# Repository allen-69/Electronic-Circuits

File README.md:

PCB Designing Course Internship June 2026 by Allen Joshua S

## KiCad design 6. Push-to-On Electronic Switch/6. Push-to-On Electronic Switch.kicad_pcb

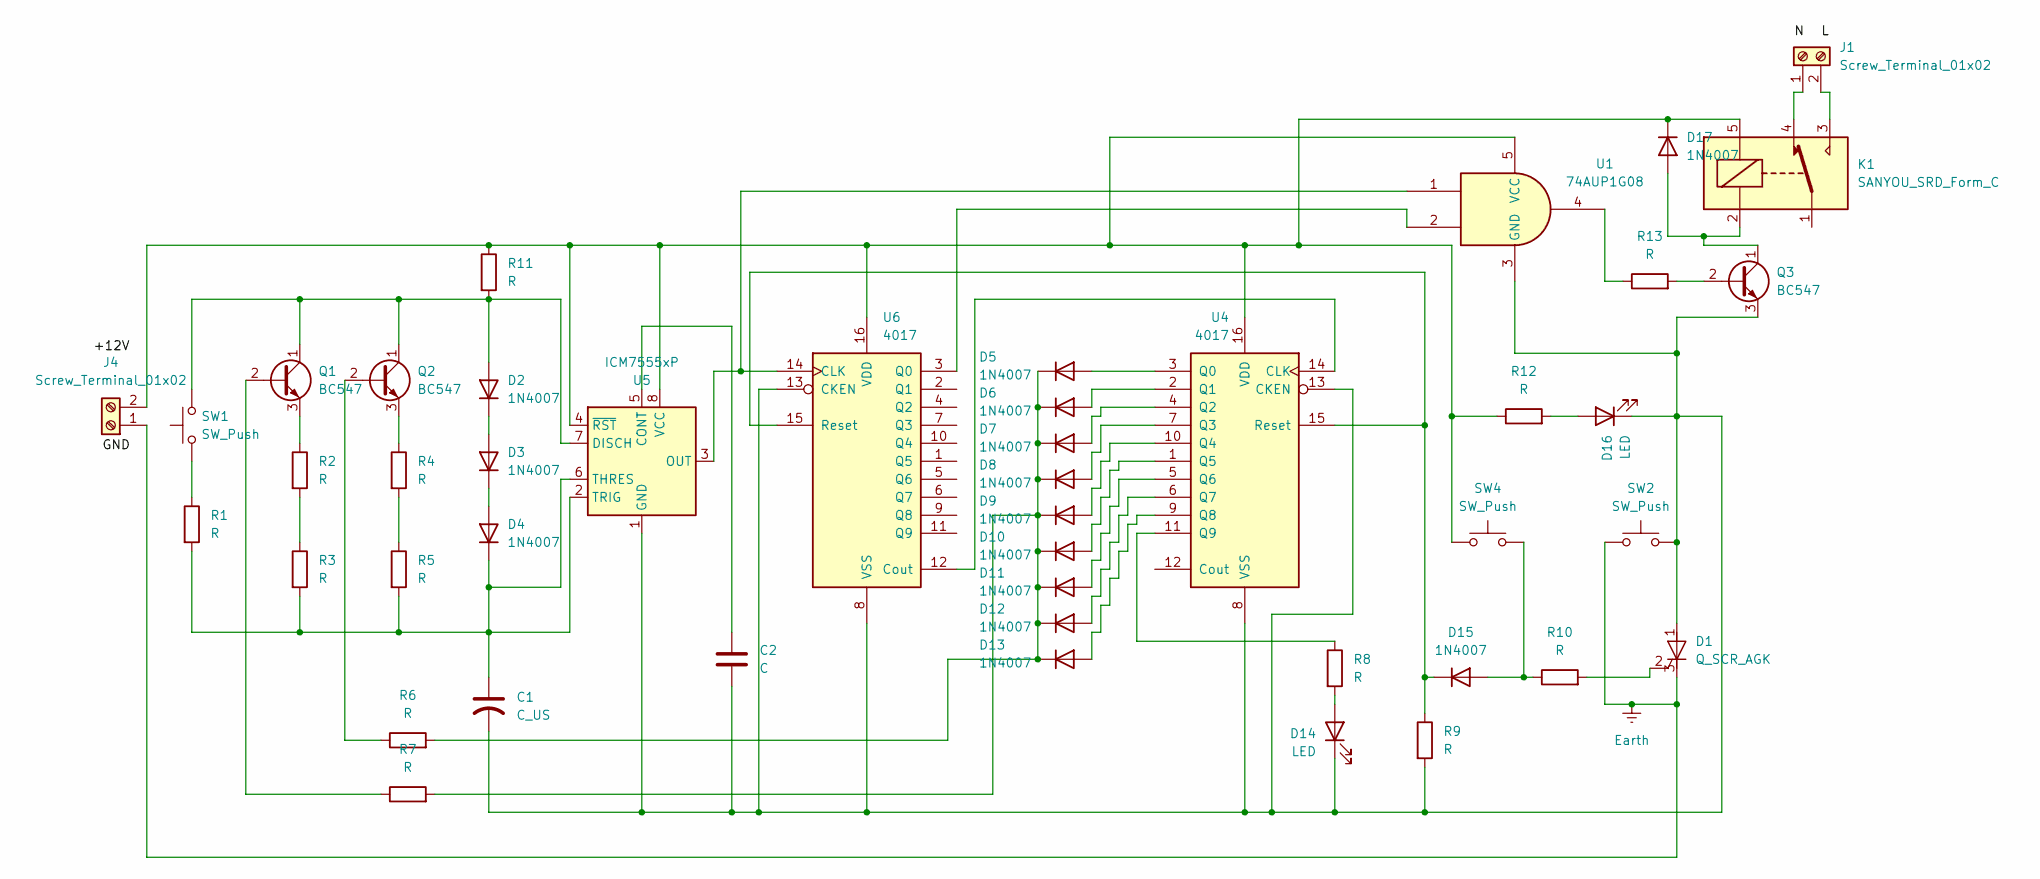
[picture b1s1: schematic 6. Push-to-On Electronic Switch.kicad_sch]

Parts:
C1: C_US; C_Radial_D4.0mm_H5.0mm_P1.50mm
C2: C; C_Radial_D5.0mm_H5.0mm_P2.00mm
D1: Q_SCR_AGK; TO-220-3_Vertical
D2, D3, D4, D5, D6, D7, D8, D9, D10, D11, D12, D13, D15, D17: 1N4007; D_DO-41_SOD81_P10.16mm_Horizontal
D14, D16: LED; LED_D3.0mm
J1, J4: Screw_Terminal_01x02; TerminalBlock_RND_205-00067_1x02_P7.50mm_Horizontal
K1: SANYOU_SRD_Form_C; Relay_SPDT_SANYOU_SRD_Series_Form_C
Q1, Q2, Q3: BC547; TO-92_Inline
R1, R2, R3, R4, R5, R6, R7, R8, R9, R10, R11, R12, R13: R; R_Axial_DIN0207_L6.3mm_D2.5mm_P15.24mm_Horizontal
SW1, SW2, SW4: SW_Push; SW_Tactile_Straight_KSA0Axx1LFTR
U1: 74AUP1G08; Texas_R-PDSO-G5_DCK-5
U4, U6: 4017; CERDIP-16_W7.62mm_SideBrazed_LongPads
U5: ICM7555xP; DIP-8_W7.62mm

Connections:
Earth: D1.3 (K), J4.1, SW2.1
unnamed: C1.2, C2.2, D1.1 (A), D14.1 (K), D16.1 (K), Q3.3 (E), R9.2, SW2.2, U1.3 (GND), U4.8 (VSS), U4.13 (CKEN), U5.1 (GND), U6.8 (VSS), U6.13 (CKEN)
unnamed: D1.2 (G), R10.2
unnamed: D2.2 (A), Q1.1 (C), Q2.1 (C), R11.2, SW1.2, U5.7 (DISCH)
unnamed: D2.1 (K), D3.2 (A)
unnamed: D3.1 (K), D4.2 (A)
unnamed: C1.1, D4.1 (K), R1.2, R3.2, R5.2, U5.2 (TRIG), U5.6 (THRES)
unnamed: D5.2 (A), U4.3 (Q0)
unnamed: D6.2 (A), U4.2 (Q1)
unnamed: D7.2 (A), U4.4 (Q2)
unnamed: D8.2 (A), U4.7 (Q3)
unnamed: D9.2 (A), U4.10 (Q4)
unnamed: D10.2 (A), U4.1 (Q5)
unnamed: D5.1 (K), D6.1 (K), D7.1 (K), D8.1 (K), D9.1 (K), D10.1 (K), D11.1 (K), D12.1 (K), D13.1 (K), R6.2, R7.2
unnamed: D11.2 (A), U4.5 (Q6)
unnamed: D12.2 (A), U4.6 (Q7)
unnamed: D13.2 (A), U4.9 (Q8)
unnamed: D14.2 (A), R8.2
unnamed: D15.2 (A), R10.1, SW4.2
unnamed: D15.1 (K), R9.1, U4.15 (Reset), U6.15 (Reset)
unnamed: D16.2 (A), R12.2
unnamed: D17.2 (A), K1.2, Q3.1 (C)
unnamed: D17.1 (K), J4.2, K1.5, R11.1, R12.1, SW4.1, U1.5 (VCC), U4.16 (VDD), U5.4 (~RST), U5.8 (VCC), U6.16 (VDD)
unnamed: J1.1, K1.4
unnamed: J1.2, K1.3
unnamed: Q1.2 (B), R7.1
unnamed: Q1.3 (E), R2.1
unnamed: Q2.2 (B), R6.1
unnamed: Q2.3 (E), R4.1
unnamed: Q3.2 (B), R13.2
unnamed: R1.1, SW1.1
unnamed: R2.2, R3.1
unnamed: R4.2, R5.1
unnamed: R13.1, U1.4
unnamed: U4.14 (CLK), U6.12 (Cout)
unnamed: R8.1, U4.11 (Q9)
unnamed: C2.1, U5.5 (CONT)
unnamed: U1.1, U5.3 (OUT), U6.14 (CLK)
unnamed: U1.2, U6.3 (Q0)

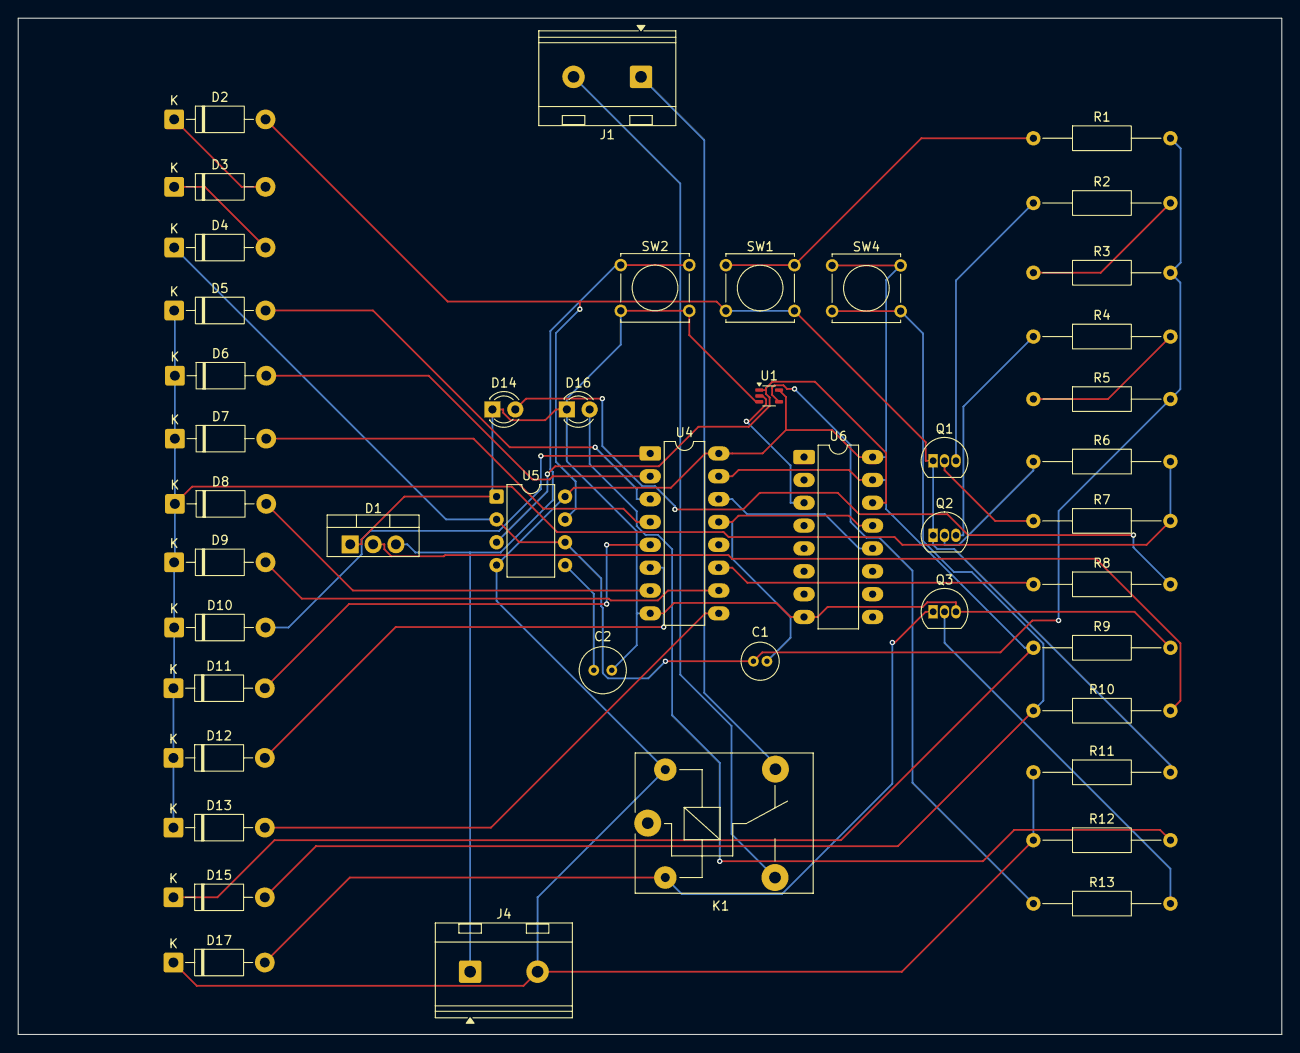
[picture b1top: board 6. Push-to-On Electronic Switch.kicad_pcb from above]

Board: 2 copper layers, 140.5 x 113.0 mm, 45 parts (0 on the bottom side), 39 nets.

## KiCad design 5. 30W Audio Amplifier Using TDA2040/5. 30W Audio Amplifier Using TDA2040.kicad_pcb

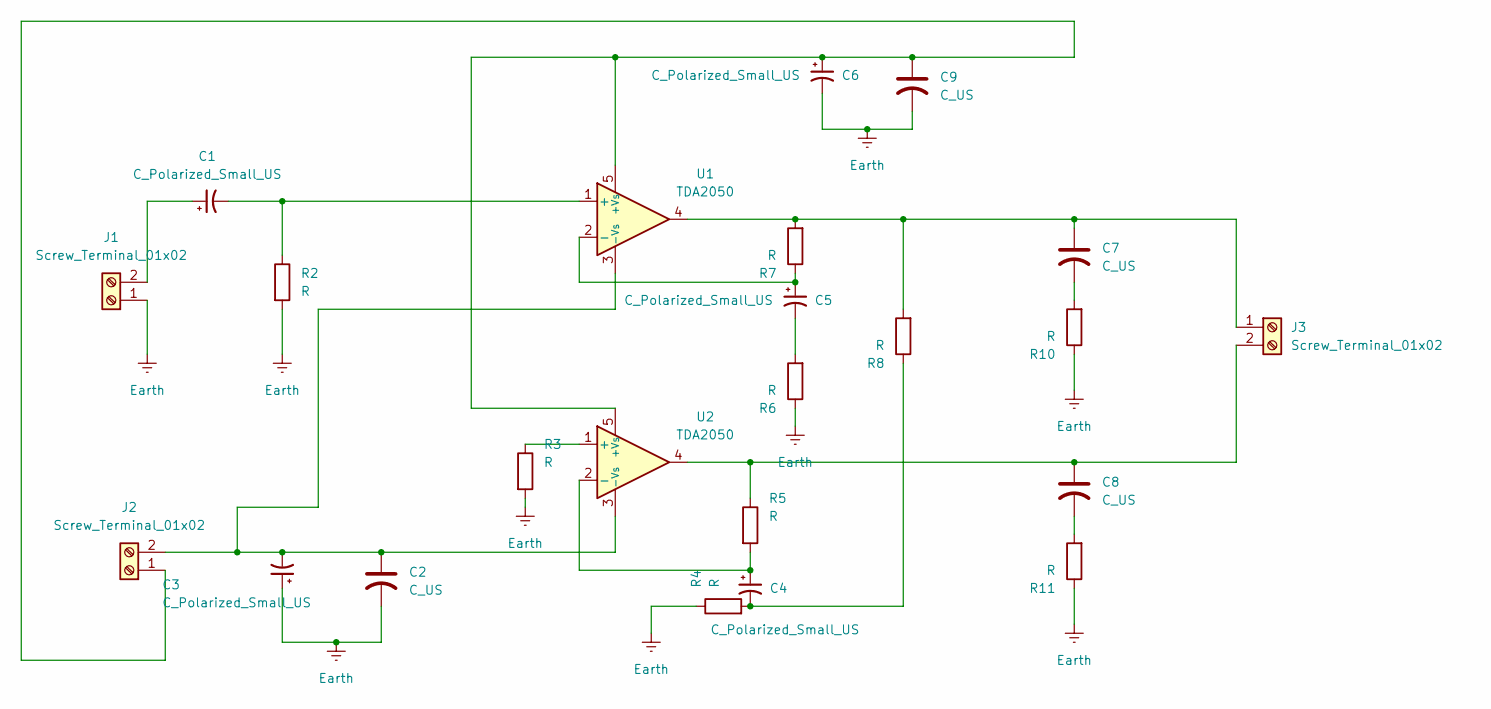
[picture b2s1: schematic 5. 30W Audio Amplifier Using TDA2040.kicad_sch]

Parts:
C1, C3, C4, C5, C6: C_Polarized_Small_US; CP_Radial_Tantal_D8.0mm_P5.00mm
C2, C7, C8, C9: C_US; C_Radial_D6.3mm_H5.0mm_P2.50mm
J1, J2, J3: Screw_Terminal_01x02; TerminalBlock_RND_205-00001_1x02_P5.00mm_Horizontal
R2, R3, R4, R5, R6, R7, R8, R10, R11: R; R_Axial_DIN0309_L9.0mm_D3.2mm_P12.70mm_Horizontal
U1, U2: TDA2050; TO-220-5_P3.4x3.7mm_StaggerOdd_Lead3.8mm_Vertical

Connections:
Earth: C2.2, C3.1, C6.2, C9.2, J1.1, R2.2, R3.2, R4.1, R6.1, R10.1, R11.1
unnamed: C4.2, R4.2, R8.1
unnamed: C5.2, R6.2
unnamed: C7.2, R10.2
unnamed: C8.2, R11.2
unnamed: C1.1, J1.2
unnamed: C6.1, C9.1, J2.1, U1.5 (+Vs), U2.5 (+Vs)
unnamed: C2.1, C3.2, J2.2, U1.3 (-Vs), U2.3 (-Vs)
unnamed: C7.1, J3.1, R7.2, R8.2, U1.4
unnamed: C8.1, J3.2, R5.1, U2.4
unnamed: C1.2, R2.1, U1.1 (+)
unnamed: C5.1, R7.1, U1.2 (-)
unnamed: R3.1, U2.1 (+)
unnamed: C4.1, R5.2, U2.2 (-)

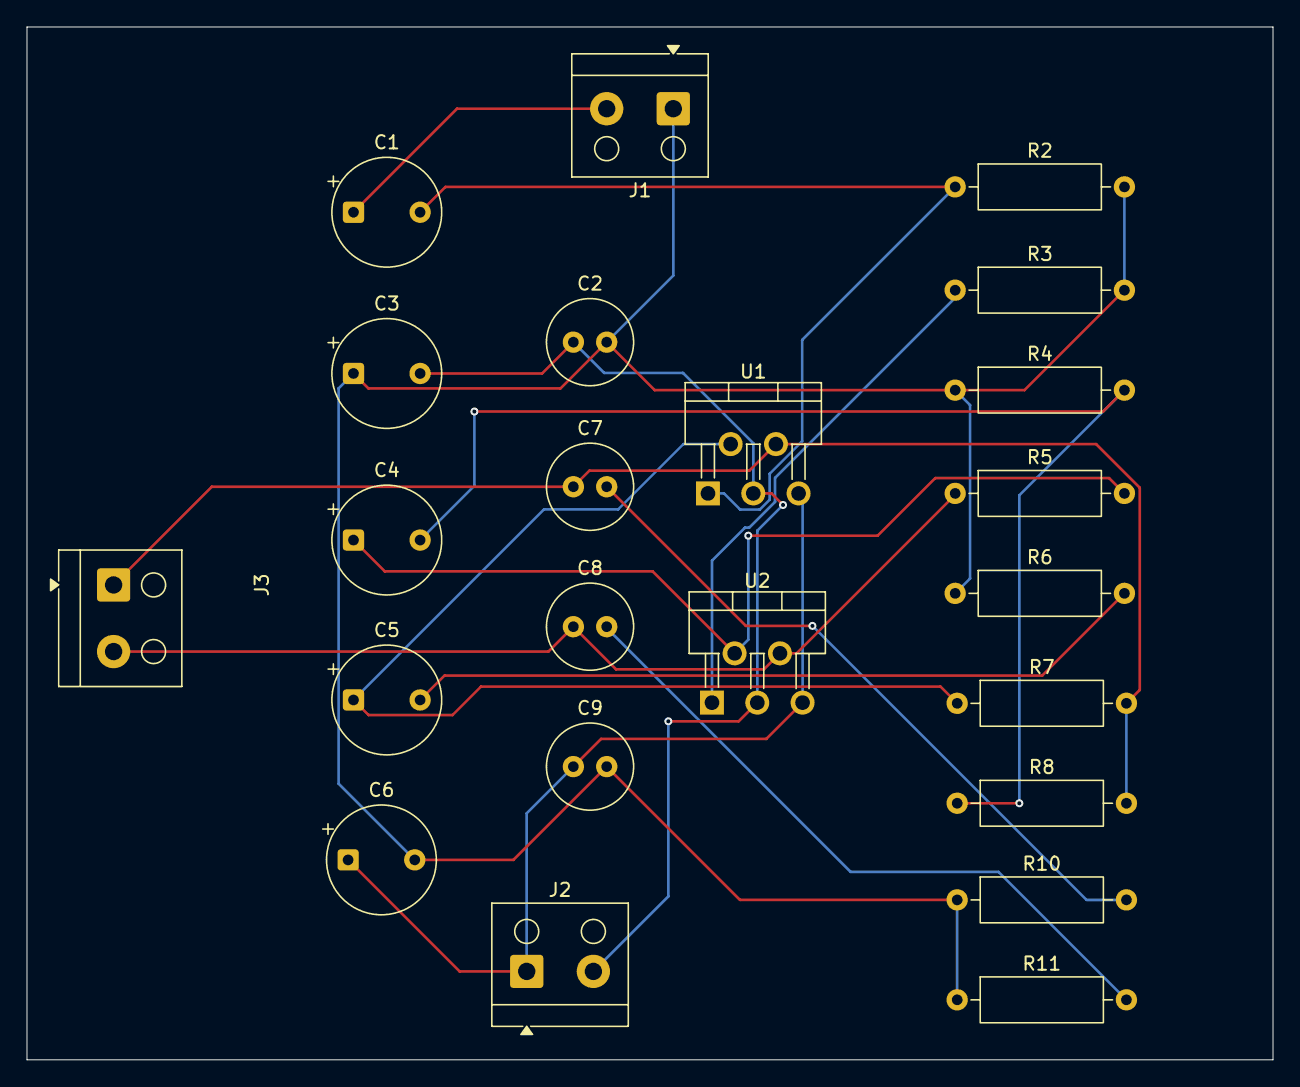
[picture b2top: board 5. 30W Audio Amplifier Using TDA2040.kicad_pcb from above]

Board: 2 copper layers, 93.5 x 77.5 mm, 23 parts (0 on the bottom side), 14 nets.

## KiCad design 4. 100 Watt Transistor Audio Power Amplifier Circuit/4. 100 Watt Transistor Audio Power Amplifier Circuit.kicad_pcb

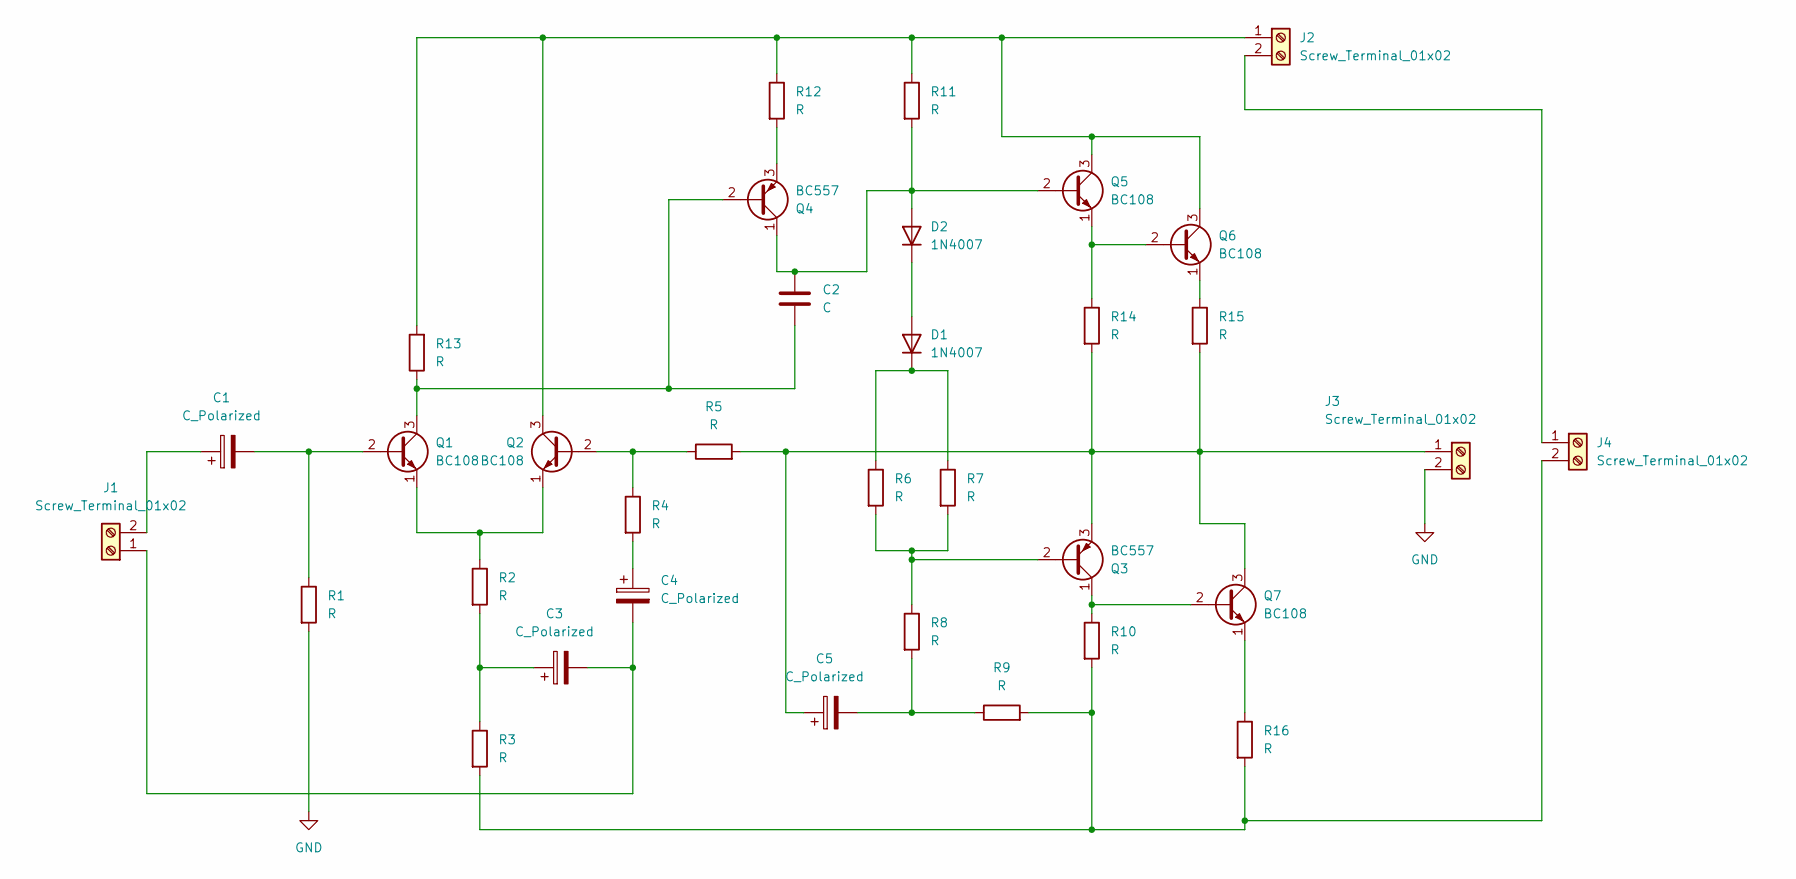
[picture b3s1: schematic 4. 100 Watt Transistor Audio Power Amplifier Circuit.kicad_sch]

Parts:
C1, C3, C4, C5: C_Polarized; CP_Radial_D13.0mm_P5.00mm
C2: C; C_Radial_D5.0mm_H11.0mm_P2.00mm
D1, D2: 1N4007; D_DO-41_SOD81_P10.16mm_Horizontal
J1, J2, J3, J4: Screw_Terminal_01x02; TerminalBlock_RND_205-00012_1x02_P5.00mm_Horizontal
Q1, Q2, Q5, Q6, Q7: BC108; TO-18-3
Q3, Q4: BC557; TO-92_Inline
R1, R2, R3, R4, R5, R6, R7, R8, R9, R10, R11, R12, R13, R14, R15, R16: R; R_Axial_DIN0207_L6.3mm_D2.5mm_P7.62mm_Horizontal

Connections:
GND: J3.2, R1.2
unnamed: C3.1, R2.2, R3.1
unnamed: C4.1, R4.2
unnamed: C5.2, R8.2, R9.1
unnamed: D1.2 (A), D2.1 (K)
unnamed: D1.1 (K), R6.1, R7.1
unnamed: C2.1, D2.2 (A), Q4.1 (C), Q5.2 (B), R11.2
unnamed: C3.2, C4.2, J1.1
unnamed: C1.1, J1.2
unnamed: J2.1, Q2.3 (C), Q5.3 (C), Q6.3 (C), R11.1, R12.1, R13.2
unnamed: J2.2, J4.1
unnamed: C5.1, J3.1, Q3.3 (E), Q7.3 (C), R5.2, R14.2, R15.2
unnamed: J4.2, R3.2, R9.2, R10.2, R16.2
unnamed: C1.2, Q1.2 (B), R1.1
unnamed: C2.2, Q1.3 (C), Q4.2 (B), R13.1
unnamed: Q1.1 (E), Q2.1 (E), R2.1
unnamed: Q2.2 (B), R4.1, R5.1
unnamed: Q3.2 (B), R6.2, R7.2, R8.1
unnamed: Q3.1 (C), Q7.2 (B), R10.1
unnamed: Q4.3 (E), R12.2
unnamed: Q5.1 (E), Q6.2 (B), R14.1
unnamed: Q6.1 (E), R15.1
unnamed: Q7.1 (E), R16.1

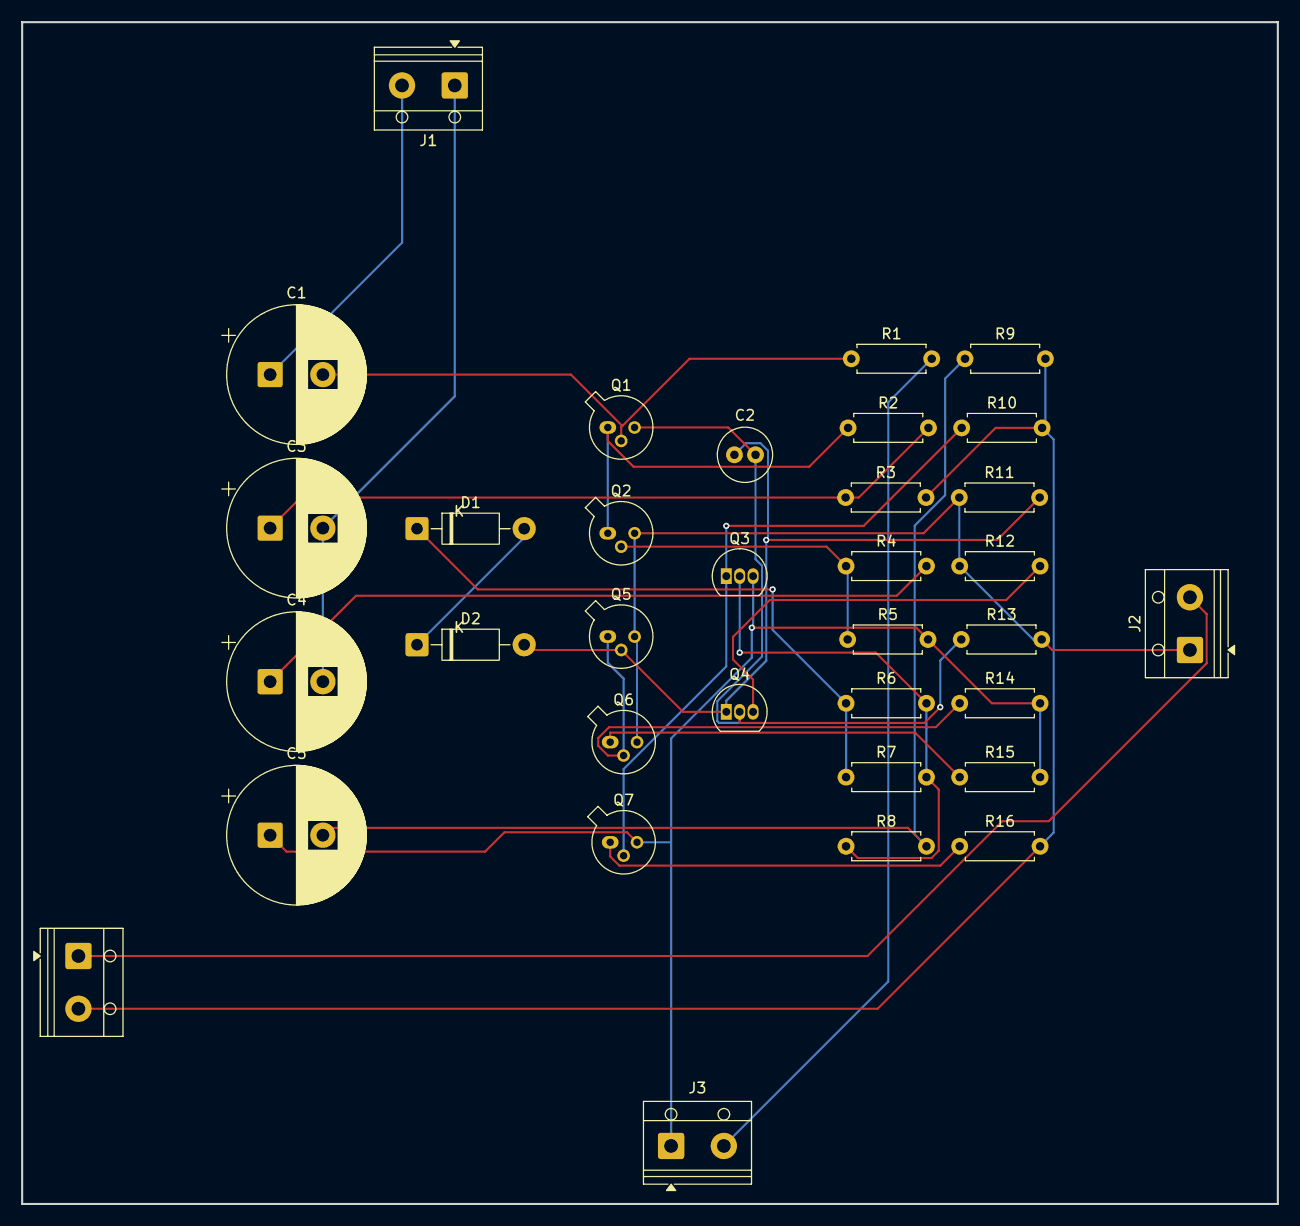
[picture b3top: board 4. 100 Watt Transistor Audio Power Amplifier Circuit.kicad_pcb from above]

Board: 2 copper layers, 119.0 x 112.0 mm, 34 parts (0 on the bottom side), 23 nets.

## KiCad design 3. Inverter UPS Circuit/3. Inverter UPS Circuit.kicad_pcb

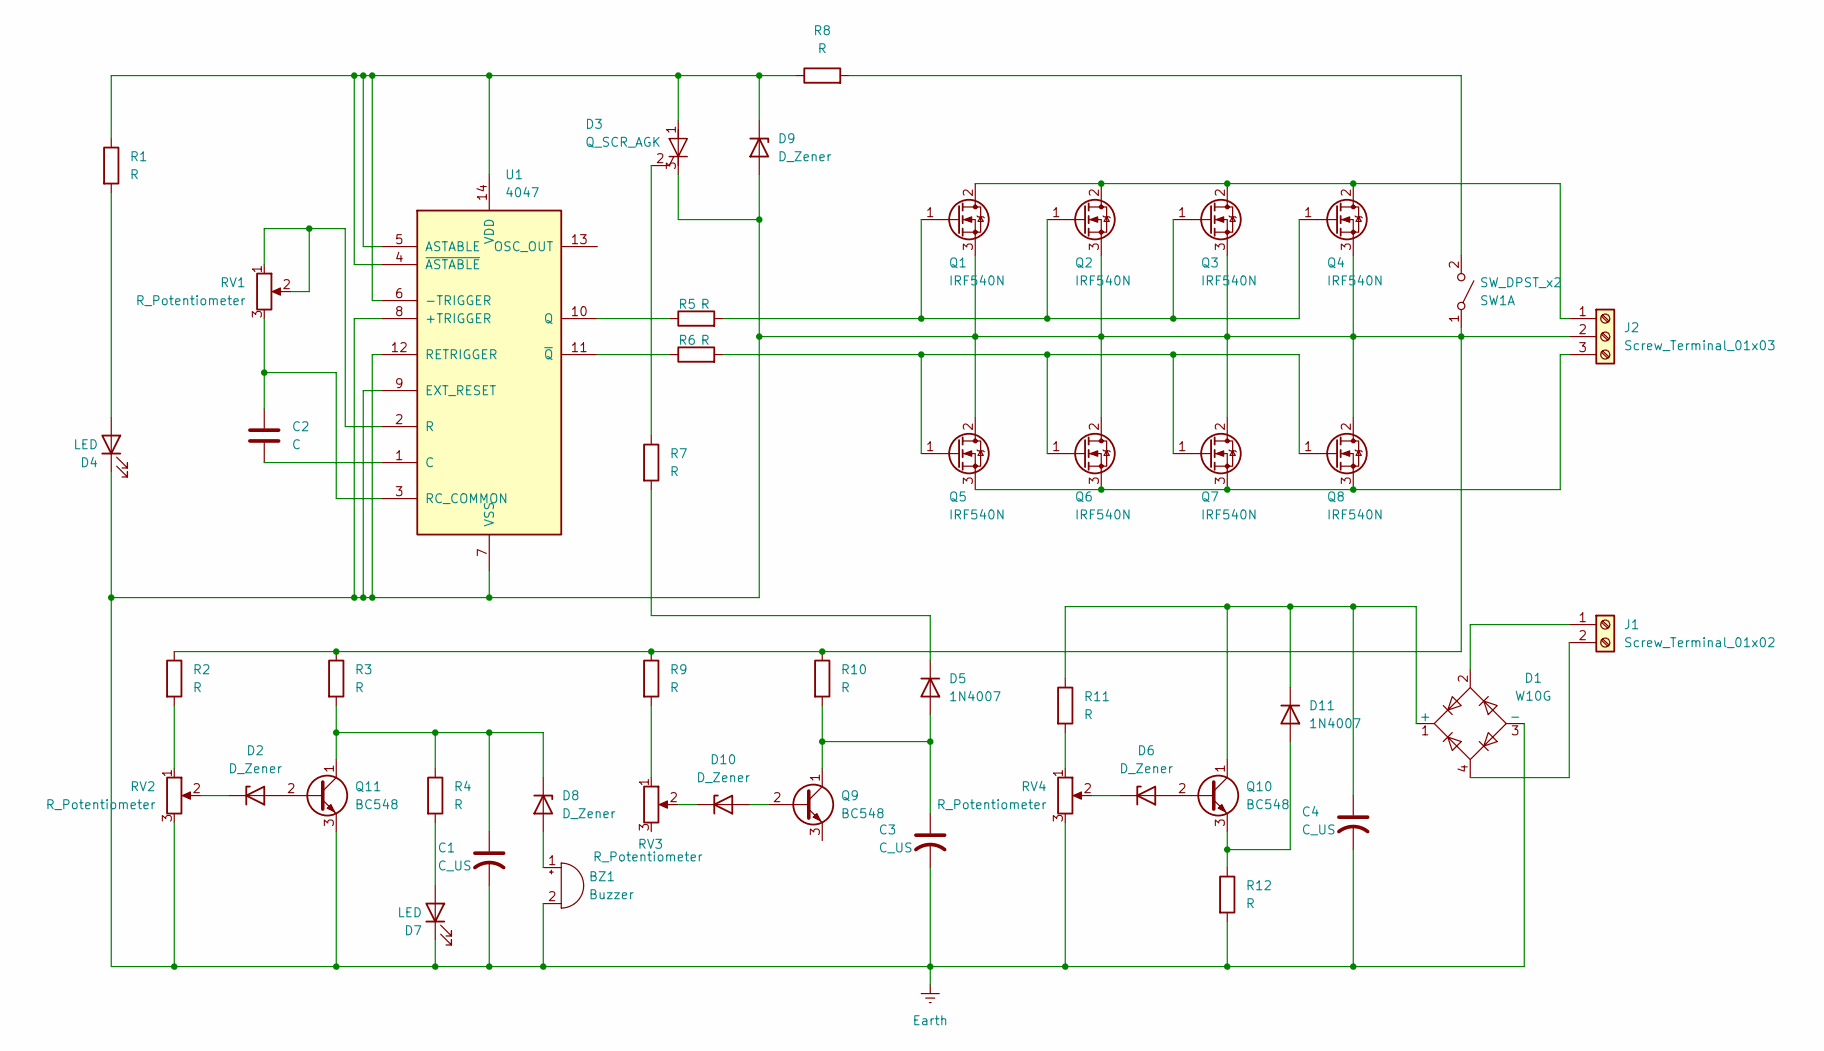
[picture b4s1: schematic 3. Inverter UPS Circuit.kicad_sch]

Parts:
BZ1: Buzzer; Buzzer_12x9.5RM7.6
C1, C3, C4: C_US; C_Radial_D4.0mm_H5.0mm_P1.50mm
C2: C; C_Radial_D6.3mm_H5.0mm_P2.50mm
D1: W10G; Diode_Bridge_Round_D9.8mm
D2, D6, D8, D9, D10: D_Zener; D_5W_P12.70mm_Horizontal
D3: Q_SCR_AGK; SW_Slide-03_Wuerth-WS-SLTV_10x2.5x6.4_P2.54mm
D4, D7: LED; LED_D3.0mm
D5, D11: 1N4007; D_DO-41_SOD81_P10.16mm_Horizontal
J1: Screw_Terminal_01x02; TerminalBlock_RND_205-00001_1x02_P5.00mm_Horizontal
J2: Screw_Terminal_01x03; TerminalBlock_RND_205-00002_1x03_P5.00mm_Horizontal
Q1, Q2, Q3, Q4, Q5, Q6, Q7, Q8: IRF540N; TO-220-3_Vertical
Q9, Q10, Q11: BC548; TO-92_Inline
R1, R2, R3, R4, R5, R6, R7, R8, R9, R10, R11, R12: R; R_Axial_DIN0204_L3.6mm_D1.6mm_P7.62mm_Horizontal
RV1, RV2, RV3, RV4: R_Potentiometer; Potentiometer_ACP_CA14V-15_Vertical
SW1: SW_DPST_x2; SW_DIP_SPSTx02_Piano_10.8x6.64mm_W7.62mm_P2.54mm
U1: 4047; DIP-14_W7.62mm_Socket

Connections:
Earth: BZ1.2 (-), C1.2, C3.2, C4.2, D1.3 (-), D3.3 (K), D4.1 (K), D7.1 (K), D9.2 (A), J2.2, Q1.3 (S), Q2.3 (S), Q3.3 (S), Q4.3 (S), Q5.2 (D), Q6.2 (D), Q7.2 (D), Q8.2 (D), Q11.3 (E), R2.1, R3.1, R9.1, R10.1, R12.2, RV2.3, RV4.3, SW1.1 (A), U1.7 (VSS), U1.8 (+TRIGGER), U1.9 (EXT_RESET), U1.12 (RETRIGGER)
unnamed: BZ1.1 (+), D8.2 (A)
unnamed: C4.1, D1.1 (+), D11.1 (K), Q10.1 (C), R11.1
unnamed: D2.2 (A), Q11.2 (B)
unnamed: D2.1 (K), RV2.2
unnamed: D3.1 (A), D9.1 (K), R1.1, R8.1, U1.4 (~ASTABLE), U1.5 (ASTABLE), U1.6 (-TRIGGER), U1.14 (VDD)
unnamed: D3.2 (G), R7.1
unnamed: D4.2 (A), R1.2
unnamed: C3.1, D5.2 (A), Q9.1 (C), R10.2
unnamed: D5.1 (K), R7.2
unnamed: D6.2 (A), Q10.2 (B)
unnamed: D6.1 (K), RV4.2
unnamed: D7.2 (A), R4.2
unnamed: C1.1, D8.1 (K), Q11.1 (C), R3.2, R4.1
unnamed: D10.2 (A), Q9.2 (B)
unnamed: D10.1 (K), RV3.2
unnamed: D11.2 (A), Q10.3 (E), R12.1
unnamed: D1.2, J1.1
unnamed: D1.4, J1.2
unnamed: J2.1, Q1.2 (D), Q2.2 (D), Q3.2 (D), Q4.2 (D)
unnamed: J2.3, Q5.3 (S), Q6.3 (S), Q7.3 (S), Q8.3 (S)
unnamed: Q1.1 (G), Q2.1 (G), Q3.1 (G), Q4.1 (G), R5.2
unnamed: Q5.1 (G), Q6.1 (G), Q7.1 (G), Q8.1 (G), R6.2
unnamed: R2.2, RV2.1
unnamed: R9.2, RV3.1
unnamed: R11.2, RV4.1
unnamed: R8.2, SW1.2 (B)
unnamed: C2.2, U1.1 (C)
unnamed: R5.1, U1.10 (Q)
unnamed: RV1.1, RV1.2, U1.2 (R)
unnamed: C2.1, RV1.3, U1.3 (RC_COMMON)
unnamed: R6.1, U1.11 (~Q)

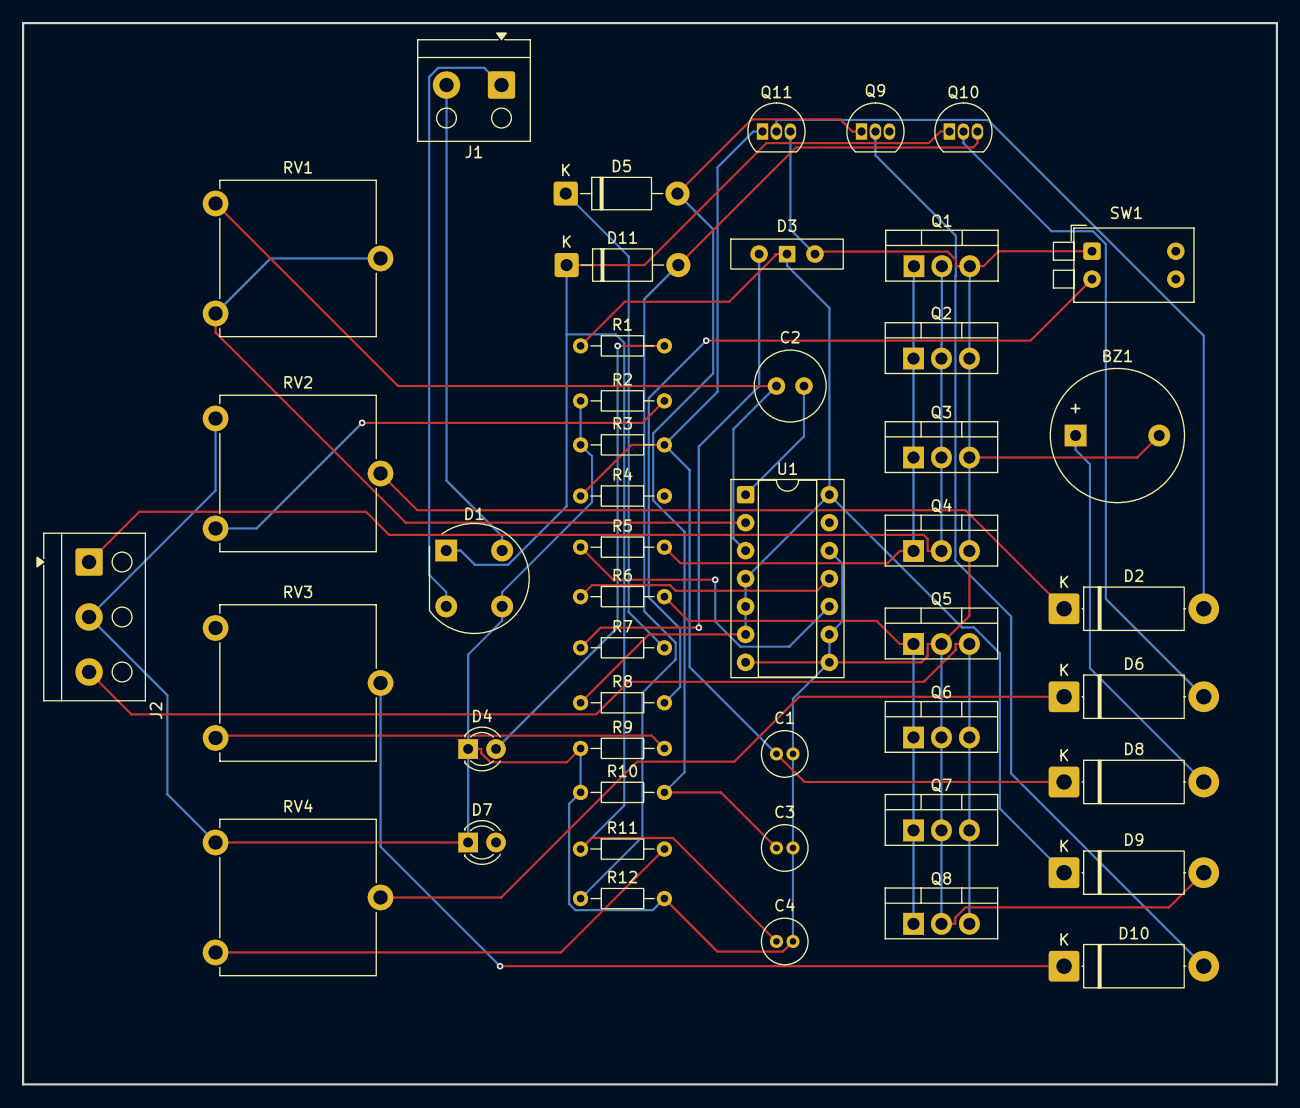
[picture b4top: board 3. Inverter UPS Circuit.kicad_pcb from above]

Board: 2 copper layers, 114.0 x 96.5 mm, 47 parts (0 on the bottom side), 32 nets.

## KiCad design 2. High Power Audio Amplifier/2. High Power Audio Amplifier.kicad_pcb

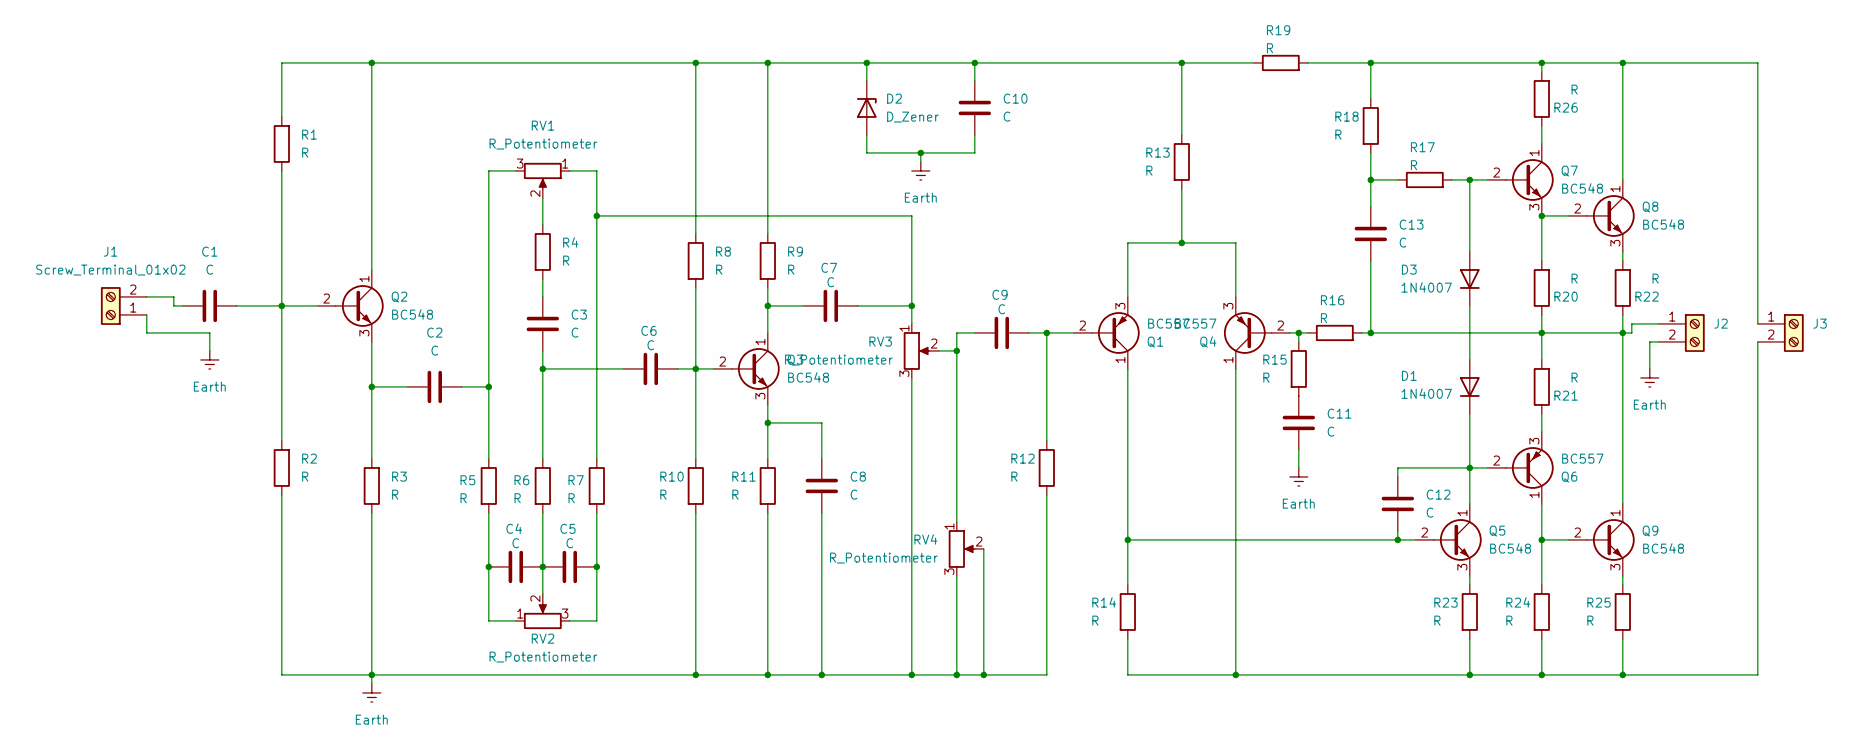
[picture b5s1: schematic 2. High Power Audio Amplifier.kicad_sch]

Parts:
C1, C2, C3, C4, C5, C6, C7, C8, C9, C10, C11, C12, C13: C; C_Radial_D4.0mm_H5.0mm_P1.50mm
D1, D3: 1N4007; D_DO-41_SOD81_P10.16mm_Horizontal
D2: D_Zener; D_5W_P10.16mm_Horizontal
J1, J2, J3: Screw_Terminal_01x02; TerminalBlock_RND_205-00001_1x02_P5.00mm_Horizontal
Q1, Q4, Q6: BC557; TO-92_Inline
Q2, Q3, Q5, Q7, Q8, Q9: BC548; TO-92_Inline
R1, R2, R3, R4, R5, R6, R7, R8, R9, R10, R11, R12, R13, R14, R15, R16, R17, R18, R19, R20, R21, R22, R23, R24, R25, R26: R; R_Axial_DIN0204_L3.6mm_D1.6mm_P7.62mm_Horizontal
RV1, RV2, RV3, RV4: R_Potentiometer; Potentiometer_ACP_CA14V-15_Vertical

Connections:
Earth: C8.1, C10.1, C11.1, D2.2 (A), J1.1, J2.2, R2.1, R3.1, R10.2, R11.2, R12.2, RV3.3, RV4.2, RV4.3
unnamed: C2.2, R5.1, RV1.3
unnamed: C3.1, C6.1, R6.1
unnamed: C3.2, R4.2
unnamed: C4.1, R5.2, RV2.1
unnamed: C4.2, C5.1, R6.2, RV2.2
unnamed: C5.2, R7.2, RV2.3
unnamed: C7.2, R7.1, RV1.1, RV3.1
unnamed: C9.1, RV3.2, RV4.1
unnamed: C11.2, R15.2
unnamed: C13.2, R17.1, R18.2
unnamed: D1.2 (A), D3.1 (K)
unnamed: C12.2, D1.1 (K), Q5.1 (C), Q6.2 (B)
unnamed: C10.2, D2.1 (K), Q2.1 (C), R1.2, R8.1, R9.1, R13.1, R19.1
unnamed: D3.2 (A), Q7.2 (B), R17.2
unnamed: C1.1, J1.2
unnamed: C13.1, J2.1, Q9.1 (C), R16.2, R20.1, R21.2, R22.1
unnamed: J3.1, Q8.1 (C), R18.1, R19.2, R26.2
unnamed: J3.2, Q4.1 (C), R14.2, R23.2, R24.2, R25.2
unnamed: C9.2, Q1.2 (B), R12.1
unnamed: C12.1, Q1.1 (C), Q5.2 (B), R14.1
unnamed: Q1.3 (E), Q4.3 (E), R13.2
unnamed: C1.2, Q2.2 (B), R1.1, R2.2
unnamed: C2.1, Q2.3 (E), R3.2
unnamed: C6.2, Q3.2 (B), R8.2, R10.1
unnamed: C7.1, Q3.1 (C), R9.2
unnamed: C8.2, Q3.3 (E), R11.1
unnamed: Q4.2 (B), R15.1, R16.1
unnamed: Q5.3 (E), R23.1
unnamed: Q6.1 (C), Q9.2 (B), R24.1
unnamed: Q6.3 (E), R21.1
unnamed: Q7.1 (C), R26.1
unnamed: Q7.3 (E), Q8.2 (B), R20.2
unnamed: Q8.3 (E), R22.2
unnamed: Q9.3 (E), R25.1
unnamed: R4.1, RV1.2

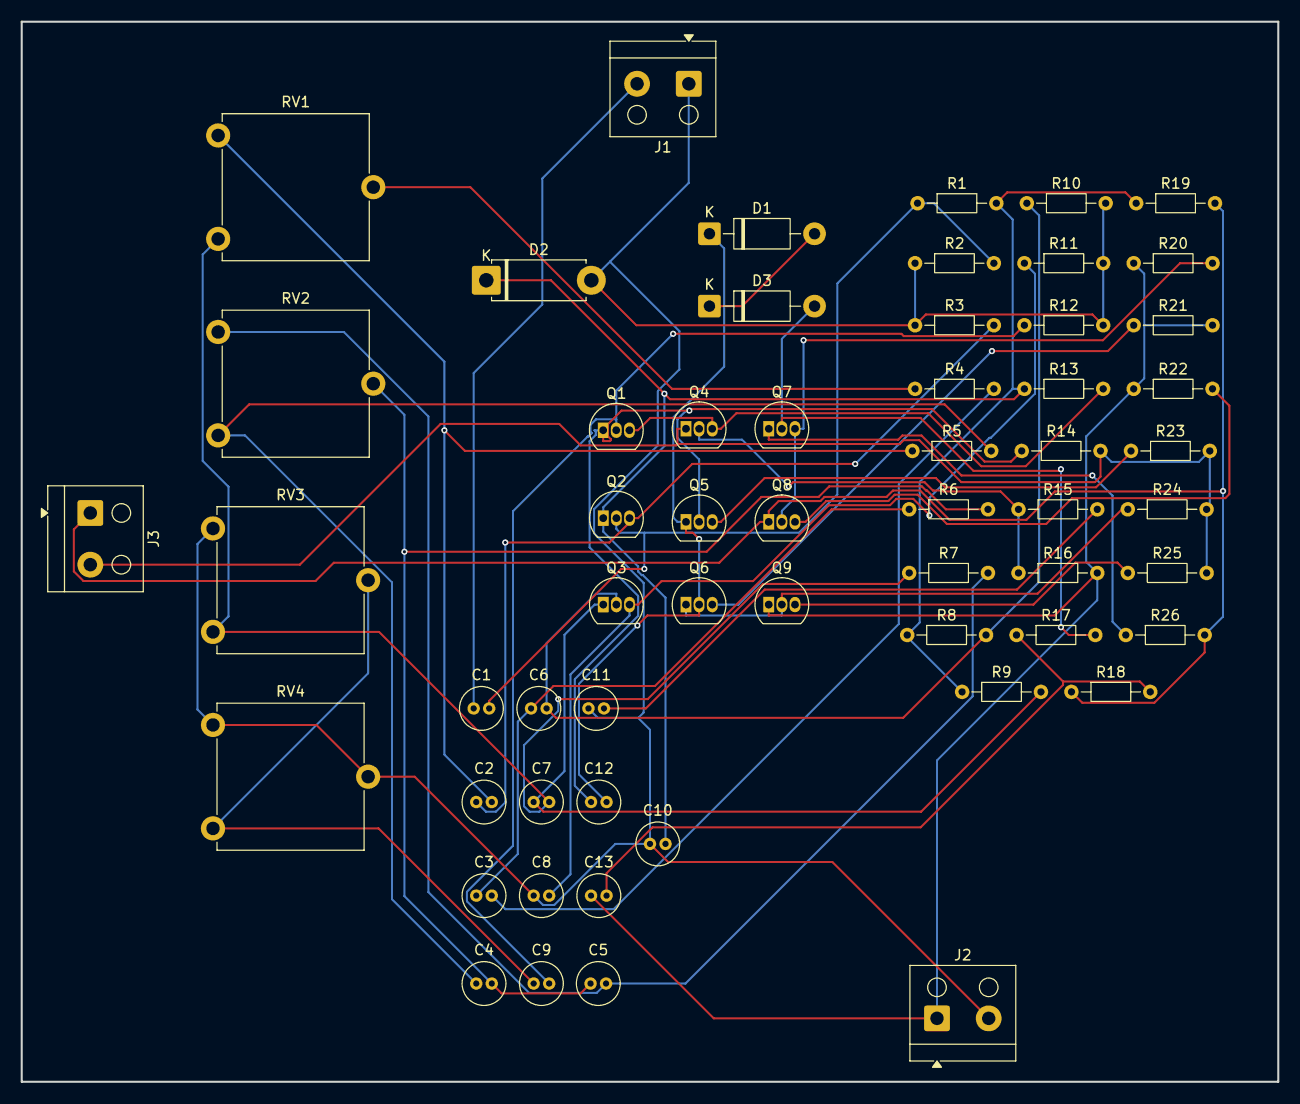
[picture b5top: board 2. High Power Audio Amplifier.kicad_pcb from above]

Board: 2 copper layers, 121.5 x 102.5 mm, 58 parts (0 on the bottom side), 36 nets.

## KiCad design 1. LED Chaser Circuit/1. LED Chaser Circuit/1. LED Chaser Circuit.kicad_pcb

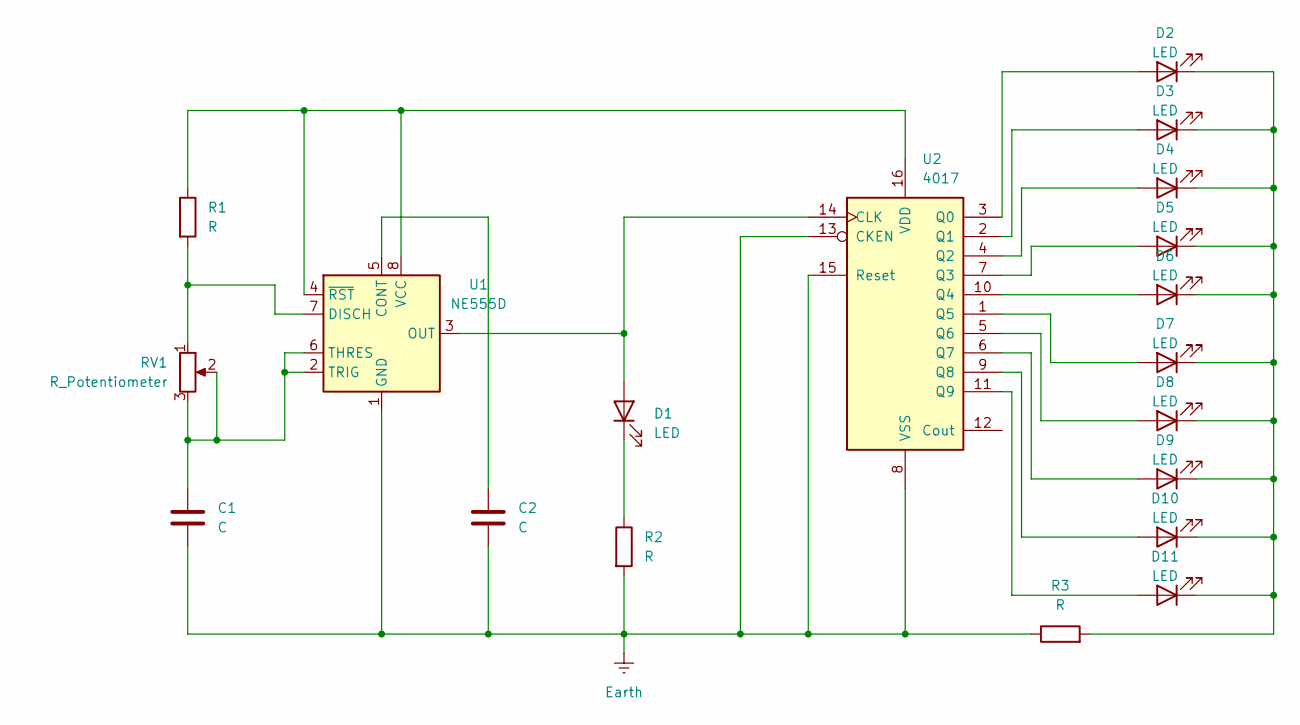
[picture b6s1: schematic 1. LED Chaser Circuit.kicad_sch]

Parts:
C1, C2: C; C_Radial_D5.0mm_H5.0mm_P2.00mm
D1, D2, D3, D4, D5, D6, D7, D8, D9, D10, D11: LED; LED_D3.0mm
R1, R2, R3: R; R_Axial_DIN0204_L3.6mm_D1.6mm_P7.62mm_Horizontal
RV1: R_Potentiometer; Potentiometer_ACP_CA14V-15_Vertical
U1: NE555D; SOIC-8_3.9x4.9mm_P1.27mm
U2: 4017

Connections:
Earth: C1.2, C2.2, R2.2, R3.1, U1.1 (GND), U2.8 (VSS), U2.13 (CKEN), U2.15 (Reset)
unnamed: D1.2 (A), U1.3 (OUT), U2.14 (CLK)
unnamed: D1.1 (K), R2.1
unnamed: D2.2 (A), U2.3 (Q0)
unnamed: D3.2 (A), U2.2 (Q1)
unnamed: D4.2 (A), U2.4 (Q2)
unnamed: D5.2 (A), U2.7 (Q3)
unnamed: D6.2 (A), U2.10 (Q4)
unnamed: D7.2 (A), U2.1 (Q5)
unnamed: D8.2 (A), U2.5 (Q6)
unnamed: D9.2 (A), U2.6 (Q7)
unnamed: D10.2 (A), U2.9 (Q8)
unnamed: D2.1 (K), D3.1 (K), D4.1 (K), D5.1 (K), D6.1 (K), D7.1 (K), D8.1 (K), D9.1 (K), D10.1 (K), D11.1 (K), R3.2
unnamed: D11.2 (A), U2.11 (Q9)
unnamed: C2.1, U1.5 (CONT)
unnamed: R1.2, RV1.1, U1.7 (DISCH)
unnamed: C1.1, RV1.2, RV1.3, U1.2 (TRIG), U1.6 (THRES)
unnamed: R1.1, U1.4 (~RST), U1.8 (VCC), U2.16 (VDD)
